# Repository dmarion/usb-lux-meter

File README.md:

USB Lux Meter
=============

Eagle PCB design and sample source code for USB Lux Meter. 
It uses CP2112 USB-to-I2C bridge and TSL2561 light to digital converter.

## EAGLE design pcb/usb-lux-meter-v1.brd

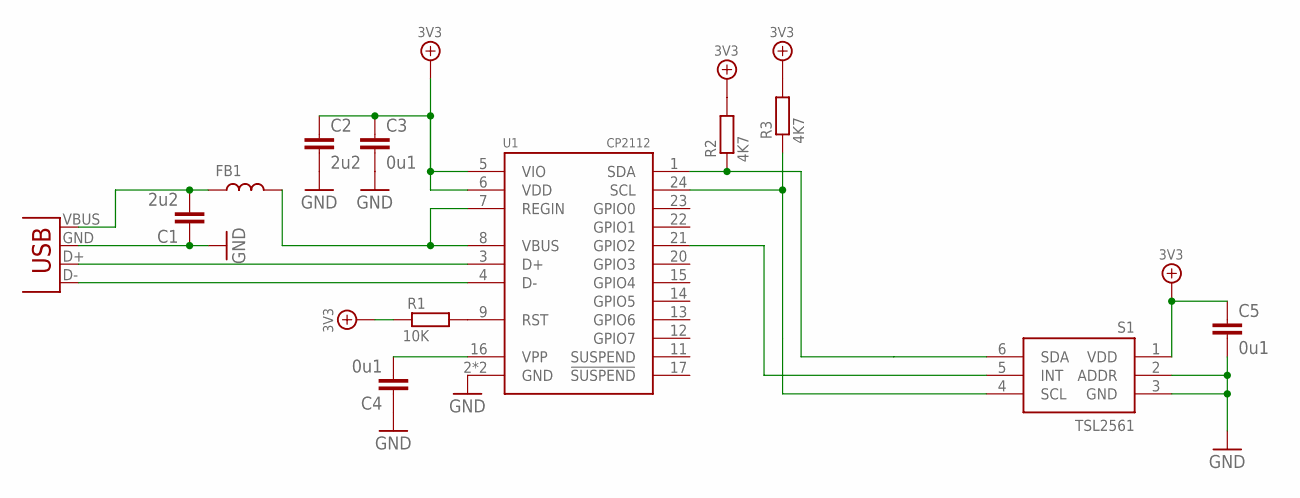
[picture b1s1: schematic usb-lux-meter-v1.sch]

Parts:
C1, C2: 2u2; C0603
C3, C4, C5: 0u1; C0603
CN1: USB-A-H
FB1: L0603; R603
R1: 10K; R603
R2, R3: 4K7; R603
S1: TSL2561
U1: CP2112; QFN24

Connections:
3V3: C2.1, C3.1, C5.1, R1.1, R2.2, R3.2, S1.1 (VDD), U1.5 (VIO), U1.6 (VDD)
CN1: CN1.D+ (D-), U1.3 (D+)
GND: C1.1, C2.2, C3.2, C4.1, C5.2, CN1.GND (VBUS), S1.2 (ADDR), S1.3 (GND), U1.2 (GND), U1.GND
unnamed: S1.5 (INT), U1.21 (GPIO2)
unnamed: R1.2, U1.9 (RST)
unnamed: C4.2, U1.16 (VPP)
unnamed: R3.1, S1.4 (SCL), U1.24 (SCL)
unnamed: C1.2, CN1.VBUS (GND), FB1.1
unnamed: R2.1, S1.6 (SDA), U1.1 (SDA)
unnamed: CN1.D- (D+), U1.4 (D-)
VBUS: FB1.2, U1.7 (REGIN), U1.8 (VBUS)

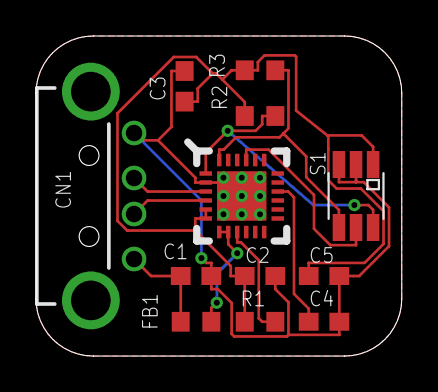
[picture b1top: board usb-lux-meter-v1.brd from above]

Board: 2 copper layers, 20.3 x 17.8 mm, 12 parts (0 on the bottom side), 11 nets.
